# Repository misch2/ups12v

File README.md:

# Goal

A hobby project to create simple 12 V UPS to backup my router and mini PC. Both appliances use 12 volts on input. 
This UPS:
 - should be powered by 18650 batteries
 - does not need to run for a long time, 15 minutes is perfectly OK, 30 minutes is luxury
 - should allow some sort of monitoring, ideally with an HomeAssistant integration (for charts etc.)
 - should provide at least this amount of power
   - 1A (for router)
   - or 3A (for mini PC)
 - should run primarily from the main source and switch to the batteries only when the main voltage drops. This is to protect the batteries and charging circuit so that it doesn't need to constantly provide relatively high power for a device.
 - might allow powering off itself on request when running on batteries, to allow mini PC to automatically power on later after a shutdown.

# Features

 - Can be controlled and monitored using HomeAssistant (ESP32C3 chip, ESPHome software)
 - 12 V / 3 A output
 - (optional) SW controllable output poweroff, can be used to power cycle the device attached to UPS
 - (optional) Battery calibration, i.e. one-off measuring of real available battery capacity.
 - (optional) UPS cut off on power loss and low battery, to allow for a full shutdown of both UPS and the attached device.

# Inspiration
* https://www.hackster.io/news/a-diy-mini-ups-for-wi-fi-router-9b8f11540294
* https://digitalab.org/2021/08/router-ups/
* Lithium battery charger module (12W, 3A) with 5V to 12V booster from Aliexpress:
https://vi.aliexpress.com/item/1005005742927465.html?gatewayAdapt=glo2vnm

# Version 1

Deployed to production, used for a backup of my Archer C6 router only. 
But it's mostly a proof of concept, with power limitations and without a proper PCB (components are just wired up together).

Schema: [schema_v1.pdf](hardware/v1/schema.pdf)

Some photos: [photo1](hardware/v1/IMG_20240301_100945.jpg), [photo2](hardware/v1/IMG_20240302_140645.jpg), [photo3](hardware/v1/IMG_20240302_140731.jpg).

"boosterEnable" input is there not to save power but to prevent running the XL6009 booster in an undervoltage condition. This could have been implemented using a voltage comparator (LM311?) + schmitt trigger for hysteresis. I used software solution because tbne undervoltage condition doesn't occur "suddenly" but it's only a startup condition. And using software to control it allows me to use it for powering off the UPS when it runs on battery.

## Development progress

Replaced AMS1117 with a buck converter due to a large voltage difference and therefore large heat dissipation with LDO.

Added XL6009 "EN" pin control (initial pull down + software control from ESP32).

Used Schottky diodes.

Added a diode between battery power line and XL6009 to prevent backpropagation of voltage when XL6009 is powered down.

The limitations were caused by:
 - BMS module for 18650 batteries can handle only 2A (FIXME?) of current. This is not enough for the mini PC.
 - INA219 module can handle only 3.2A of current. Again, this is not enough for the mini PC (especially not for the battery side of the UPS where the max current can easily be larger).
 - The specific XL6009 booster module doesn't have an undervoltage protection and it can produce more than 12 V on it's output when the input voltage is low. This is not good!

Anyway, this works well for the router. It can run for more than 2 hours from batteries because the router consumes only about 3 watts and the output current is therefore mostly below 300 mA. So I might call this a success ✅!

# Version 1.5

I wanted to overcome the limitations of the first version and to make it handle larger current to power the mini PC which might need up to 3 A. This higher current would also require something better than the INA219.

I also added relays to allow the UPS to be powered off completely when running on batteries. This is to allow the mini PC to power on automatically after a power outage. And a 2nd relay allows to power cycle the UPS or to run calibration.

ACS712 sensors paired with an ADS1115 ADC are used for current and voltage monitoring. It can handle up to 20 A. 

A pair of XL74610 ideal diodes is used instead of Schottky diodes in v1, to achieve a lower voltage drop and to allow for higher currents.

TP5100 charger module is used for charging the batteries, combined with BMS for 2S 8.4V/20A.

Alas, while everything looked good on the paper, reality was different ❌. The "better" booster module ([LM2587 version](https://www.laskakit.cz/step-up-boost-menic-lm2587--4-30v-30w/)) advertises up to 5A and 30W, but something might be wrong with it. I'm not able to pull more than 1 A from the UPS, the voltage drastically drops if I try to pull more.

Possible causes (investigating ⌛):
 - Batteries don't provide enough current? Not very probable, I'm using 3000 mAh cells from a reputable manufacturer.
 - BMS module can't handle the current? It should be able to handle 20 A but does it?
 - Booster module can't handle the current? It should be able to handle 5 A but does it?
 - Something else?

An idea: disconnect the LM2587 booster and attach an electronic load to the battery instead of it. Then try to pull whatever it takes to see if the batteries can provide the current. If they can, then the problem is with the booster. If they can't, then the problem is with the batteries or BMS.

Result: ⌛

# FIXME TODO 

Maybe this was a completely bad approach. Sticking to 2x 18650 doesn't make sense if I need to pull 3 A. I should have used 4S 18650 (13.6 V - 16.8 V) and eliminate the boost converter completely. When stepping down to 12 V, the current would be lower and the voltage drop would be lower.
Also no need to stick with 12 V and a boost converter on input.

# Version 2

Using **BQ25798** battery charger IC from Texas Instruments. According to the datasheet it can handle up to 5 A on the output and 3A on the input and has a built-in buck-boost converter usable for either battery charging or for the UPS backup mode. It can also be controlled and monitored extensively using I2C.

Product info: https://www.ti.com/product/BQ25798

Most important features:
* Buck-boost charger for 1-4 cell batteries
* Narrow voltage DC (NVDC) power path
* Backup Mode with Ultra-fast switchover to adjustable voltage
* Flexible autonomous and I2C mode for optimal system performance
* Intelligent current management to prevent source overload when charging batteries
* Integrated 16-bit ADC for voltage, current, and temperature monitoring

It's essentially a battery charger capable of using boost converter to charge the batteries, but it can also detect a drop in input voltage and switch to the backup mode aka battery mode very fast. In the backup mode it works as buck converter and uses the batteries to power the load.

So, theoretically, with this IC I can eliminate all the former external circuitry because BQ25798 will take care of both charging the batteries and providing power to the load. And it has hundreds of I2C registers to set up and monitor the system.

#### Normal mode power path:

#### Backup mode power path:

#### Inductor selection

See page 133 of datasheet:

```
L = 2.2 µH (only two inductor values are available: 2.2 µH and 1 µH)

Isat >= MAX((Iin + Iripple/2), Ichg + Iripple/2)

Iripple_buck = Vsys / Vbus * (Vbus - Vsys) / (Fsw * L)
Iripple_boost = Vbus /Vsys * (Vsys - Vbus) / (Fsw * L)
```

For my purposes (12 V input, 12 V output, 4S Li-Ion battery pack, 3 A power source) the values are:

```
Iin = 3 A (input current)
Vbus = 12 V (input voltage)
Vsys = +16.8 V (battery voltage)

Iripple_buck = 12 V / 16.8 V * (16.8 V - 12 V) / (750 kHz * 2.2 uH) = 3.43 / 1.65 = 2.08 A
Iripple_boost = 16.8 V / 12 V * (12 V - 16.8 V) / (750 kHz * 2.2 uH) = -6.72 / 1.65 = -4.07 A

Isat >= MAX(5.08 A, 7.07 A) = 7.07 A
```

#### PROG resistor selection

See page 25 of datasheet:

2.2 uH inductor requires 750 kHz switching frequency. Therefore the PROG resistor = **27 kOhm** which means:
 - Switching frequency = 750 kHz
 - Cell count: 4
 - ICHG: 1 A
 - VSYSMIN: 12 V
 - VREG: 16.8 V (range 14 V - 18.8 V)

### Principle:

#### Forward (battery charge) mode:

In this mode PMID follows VBUS, i.e. it's not regulated. PMID is also the input to the buck-boost converter. 

#### Battery backup mode:

The FETs between AC1 and VBUS provide reverse blocking (prevents battery voltage from being seen at VBUS). PMID is output of the buck/boost converter.

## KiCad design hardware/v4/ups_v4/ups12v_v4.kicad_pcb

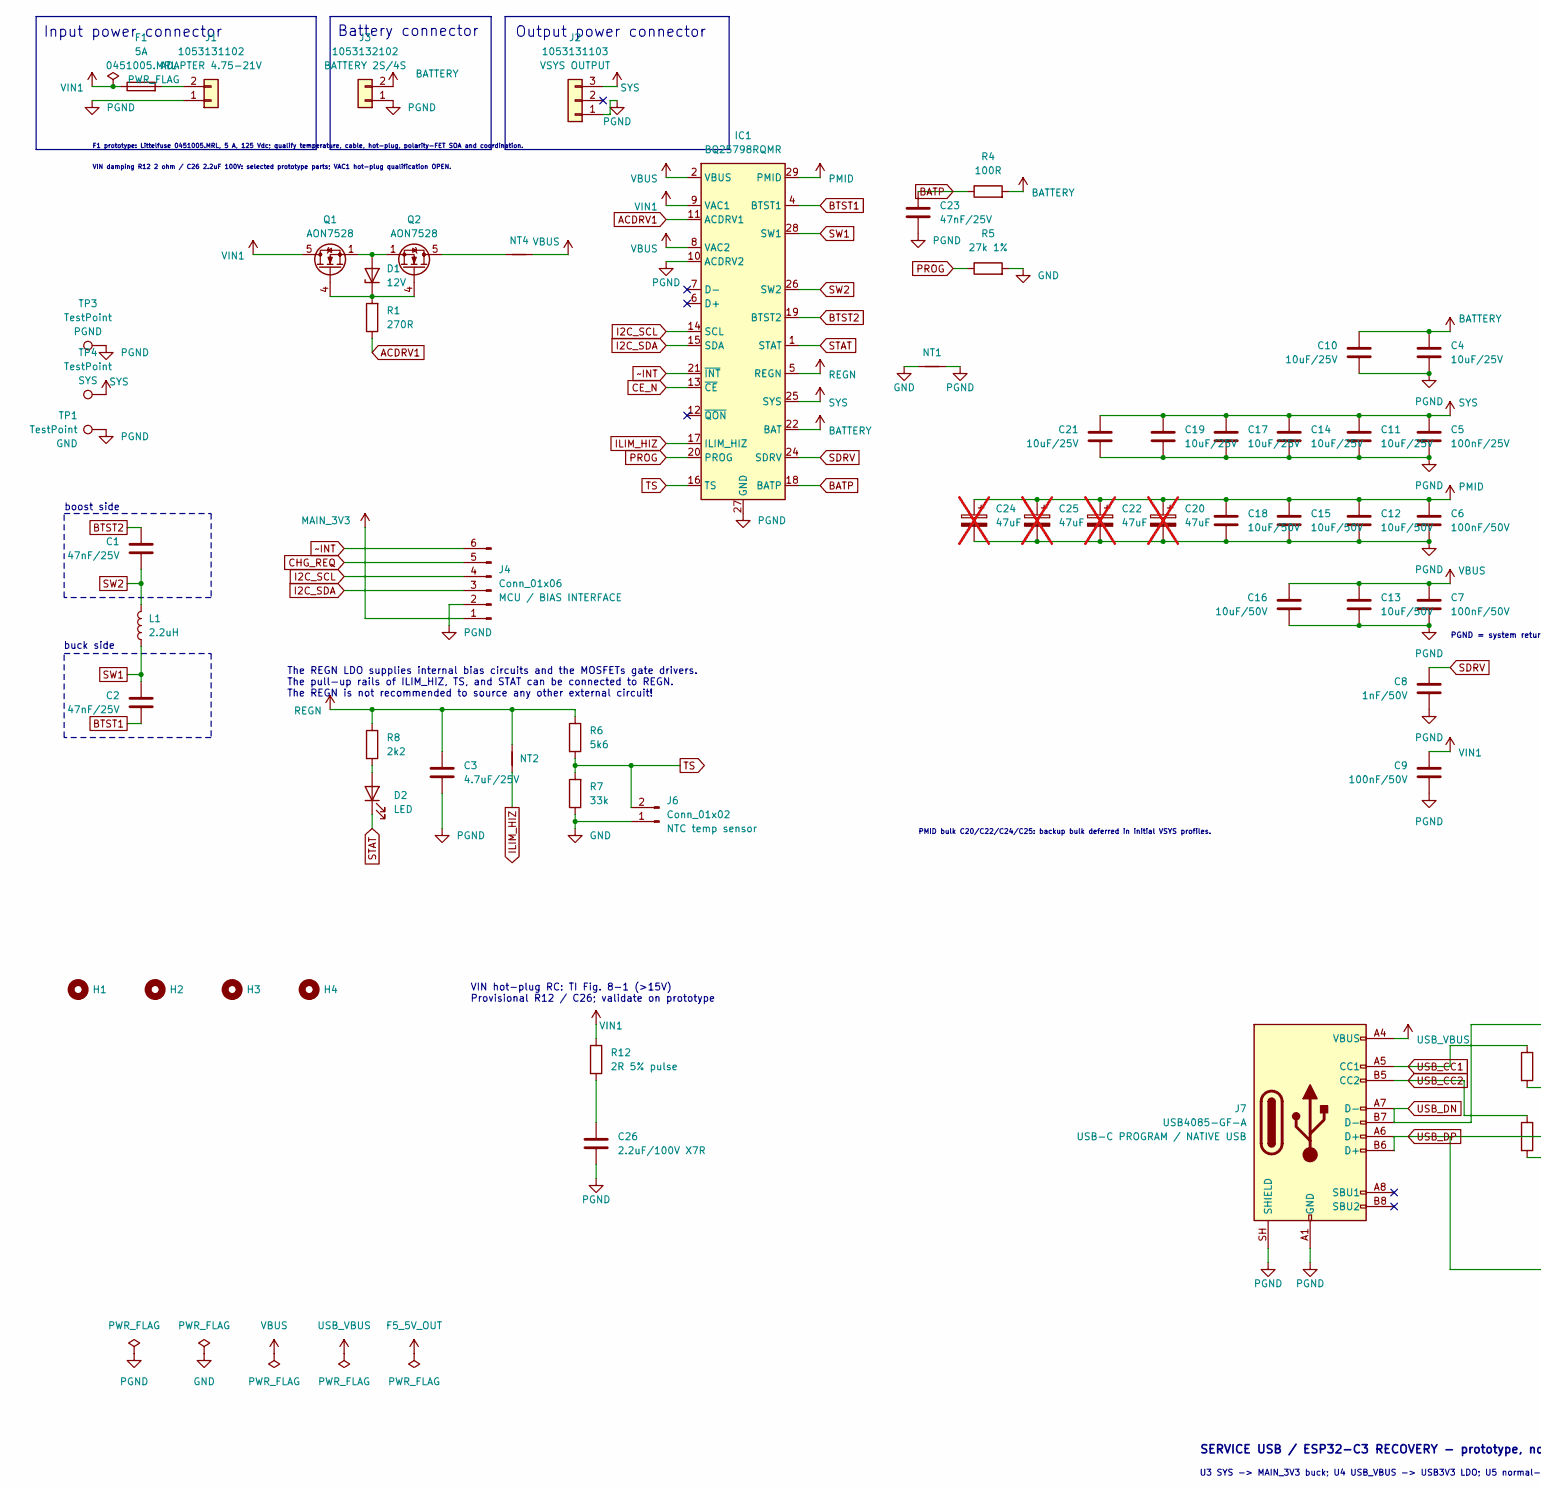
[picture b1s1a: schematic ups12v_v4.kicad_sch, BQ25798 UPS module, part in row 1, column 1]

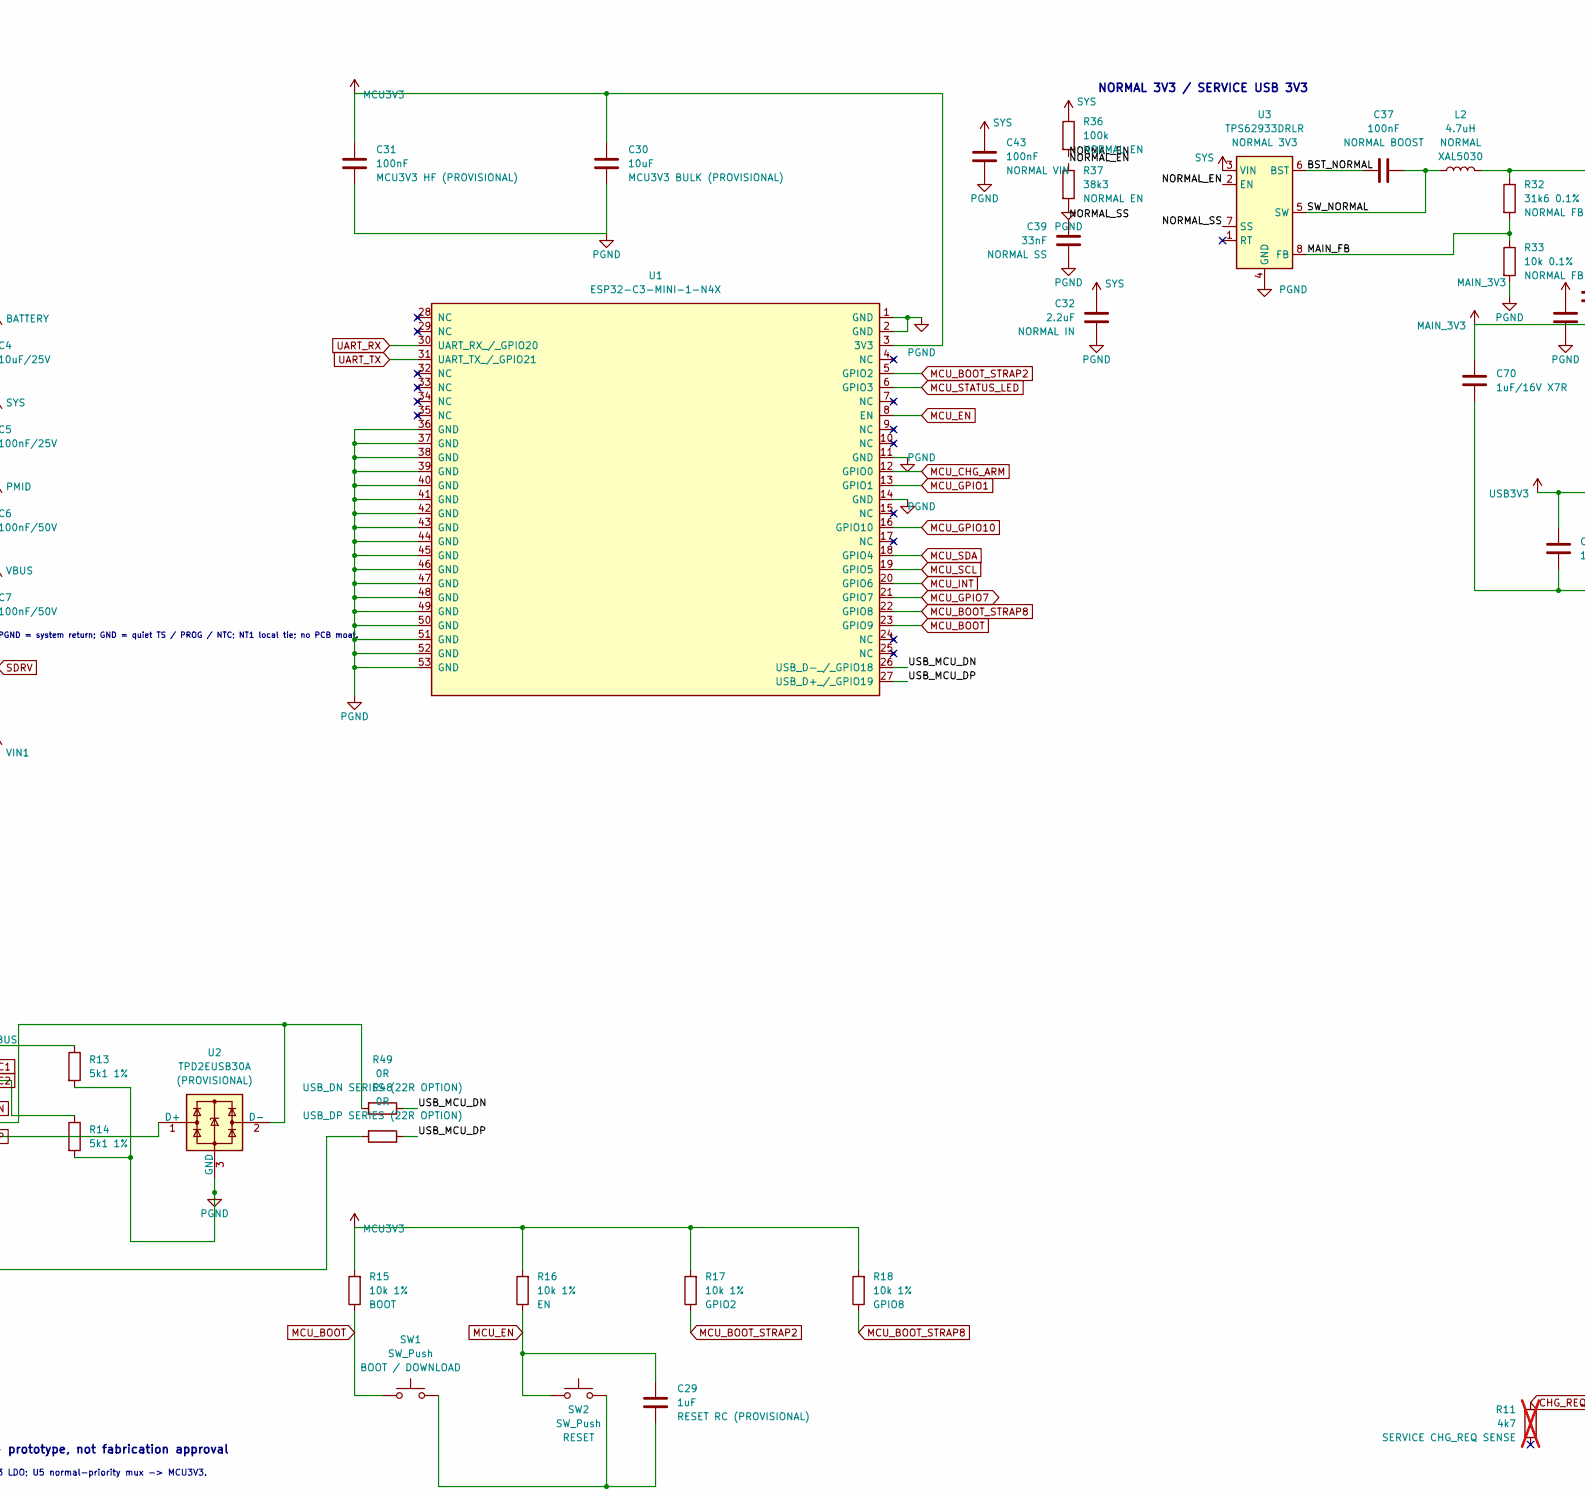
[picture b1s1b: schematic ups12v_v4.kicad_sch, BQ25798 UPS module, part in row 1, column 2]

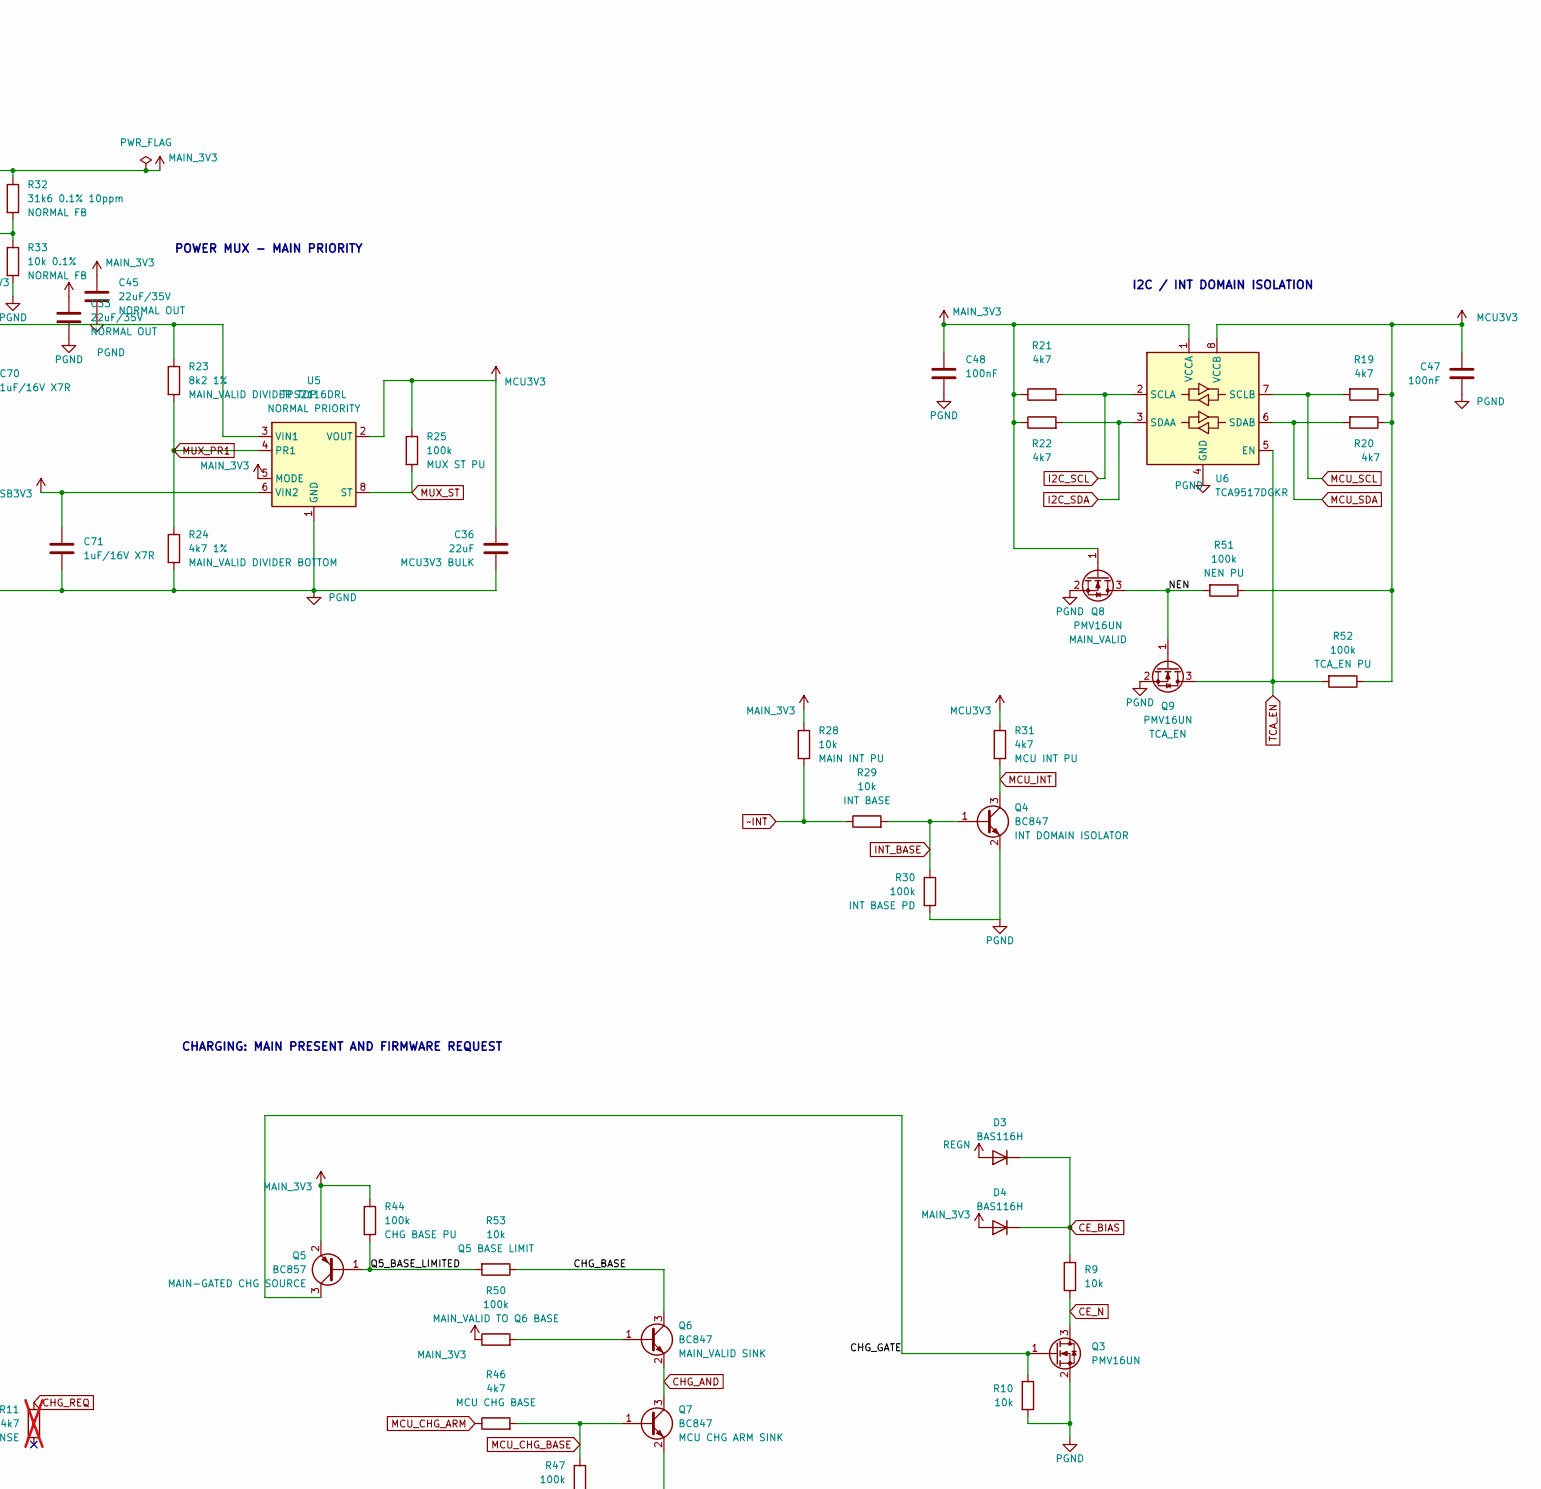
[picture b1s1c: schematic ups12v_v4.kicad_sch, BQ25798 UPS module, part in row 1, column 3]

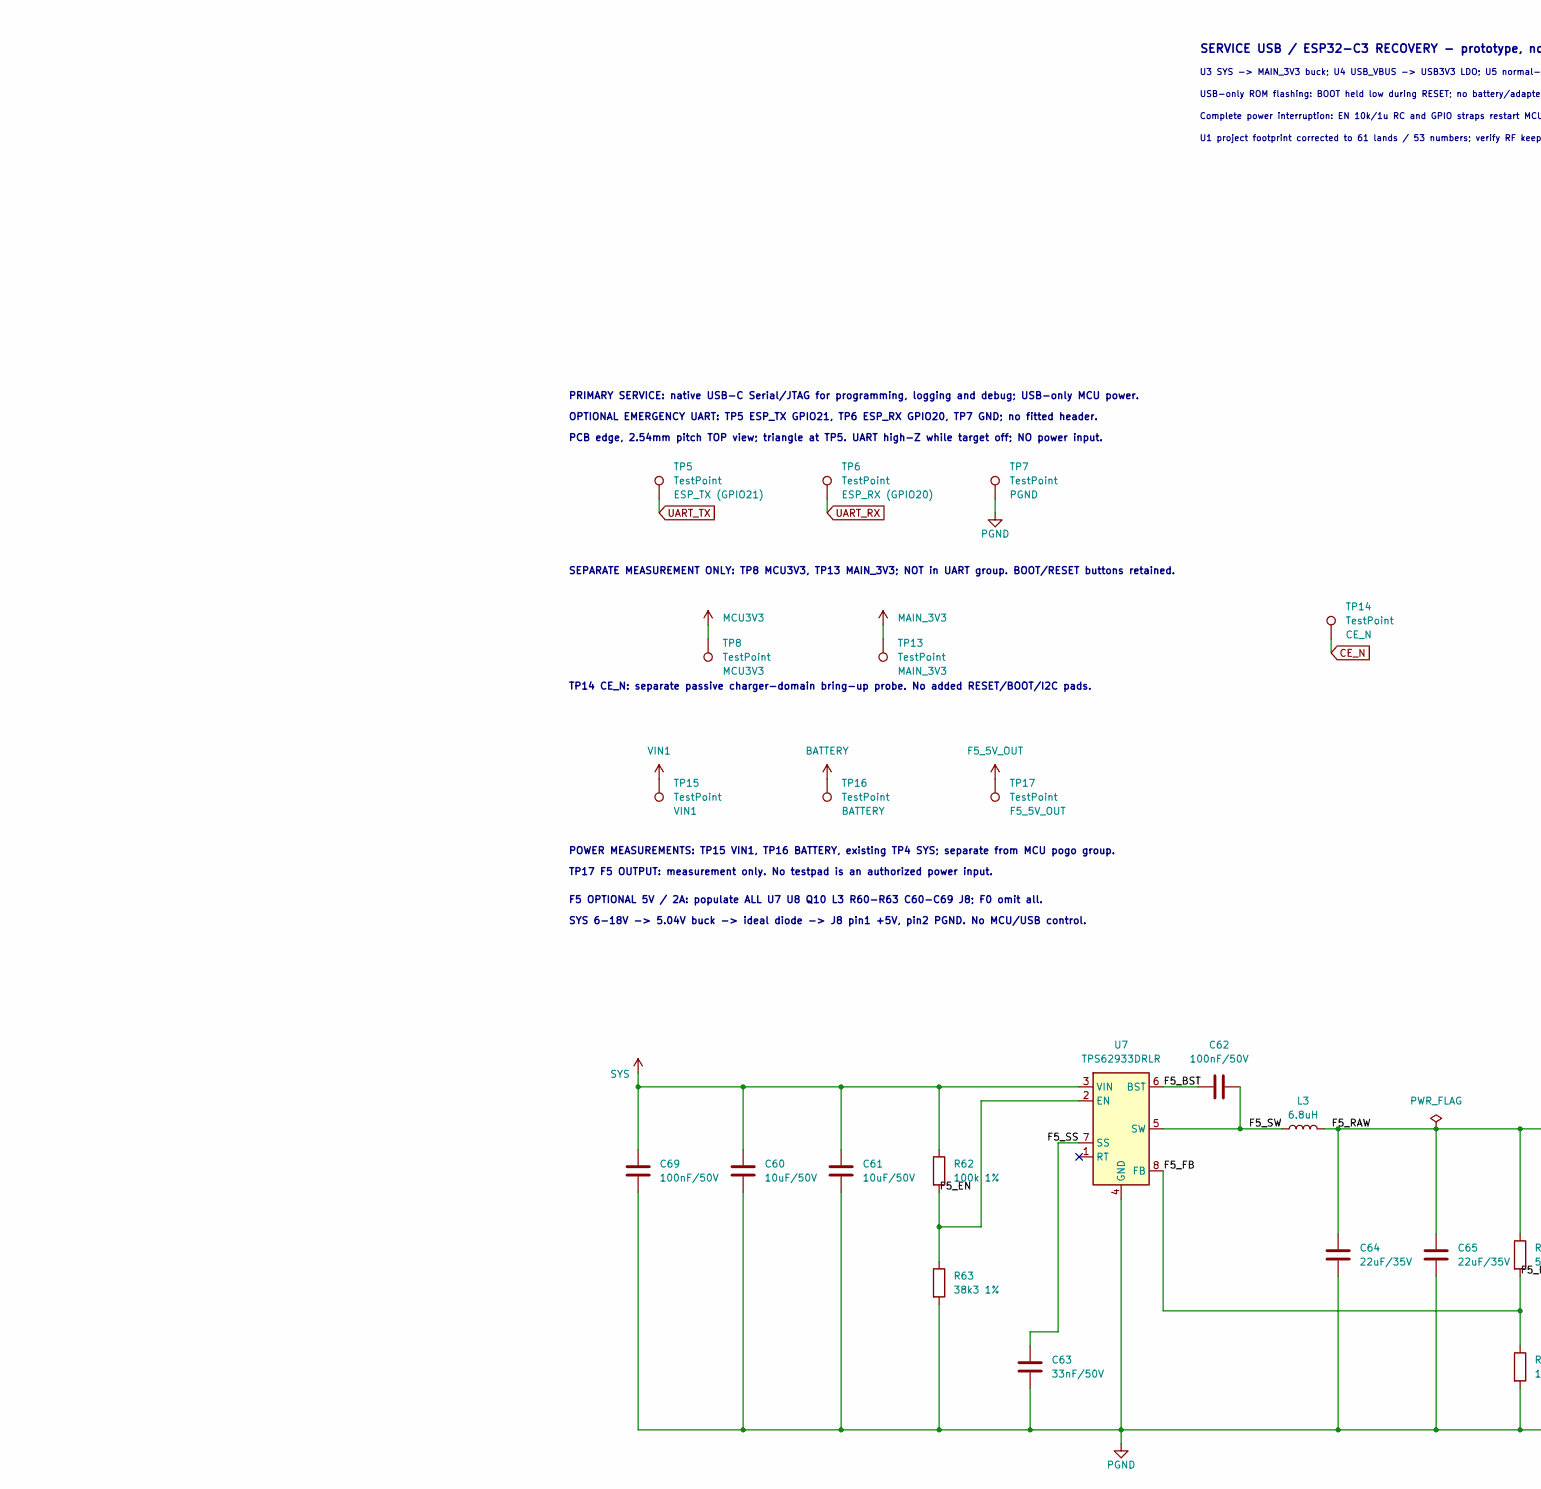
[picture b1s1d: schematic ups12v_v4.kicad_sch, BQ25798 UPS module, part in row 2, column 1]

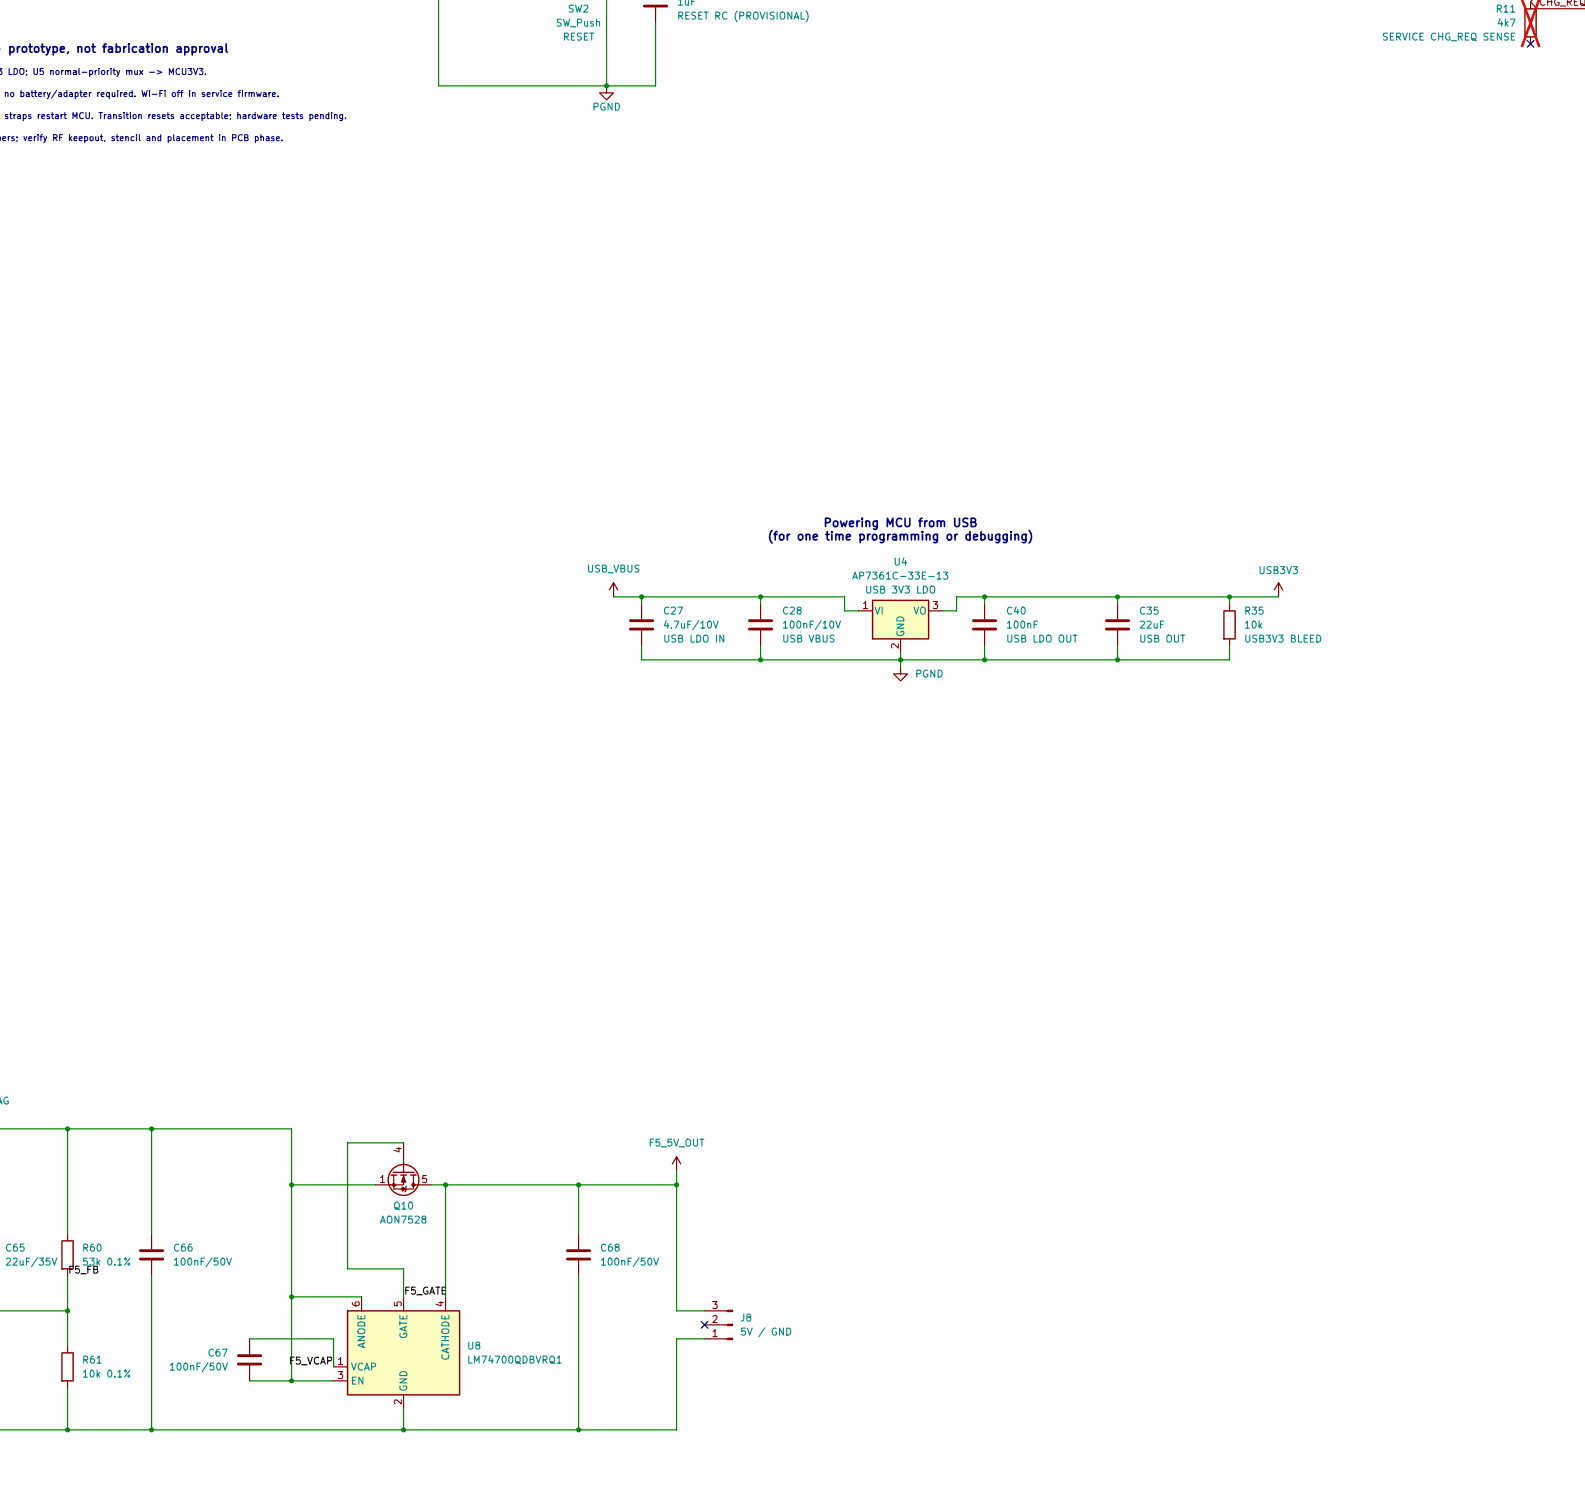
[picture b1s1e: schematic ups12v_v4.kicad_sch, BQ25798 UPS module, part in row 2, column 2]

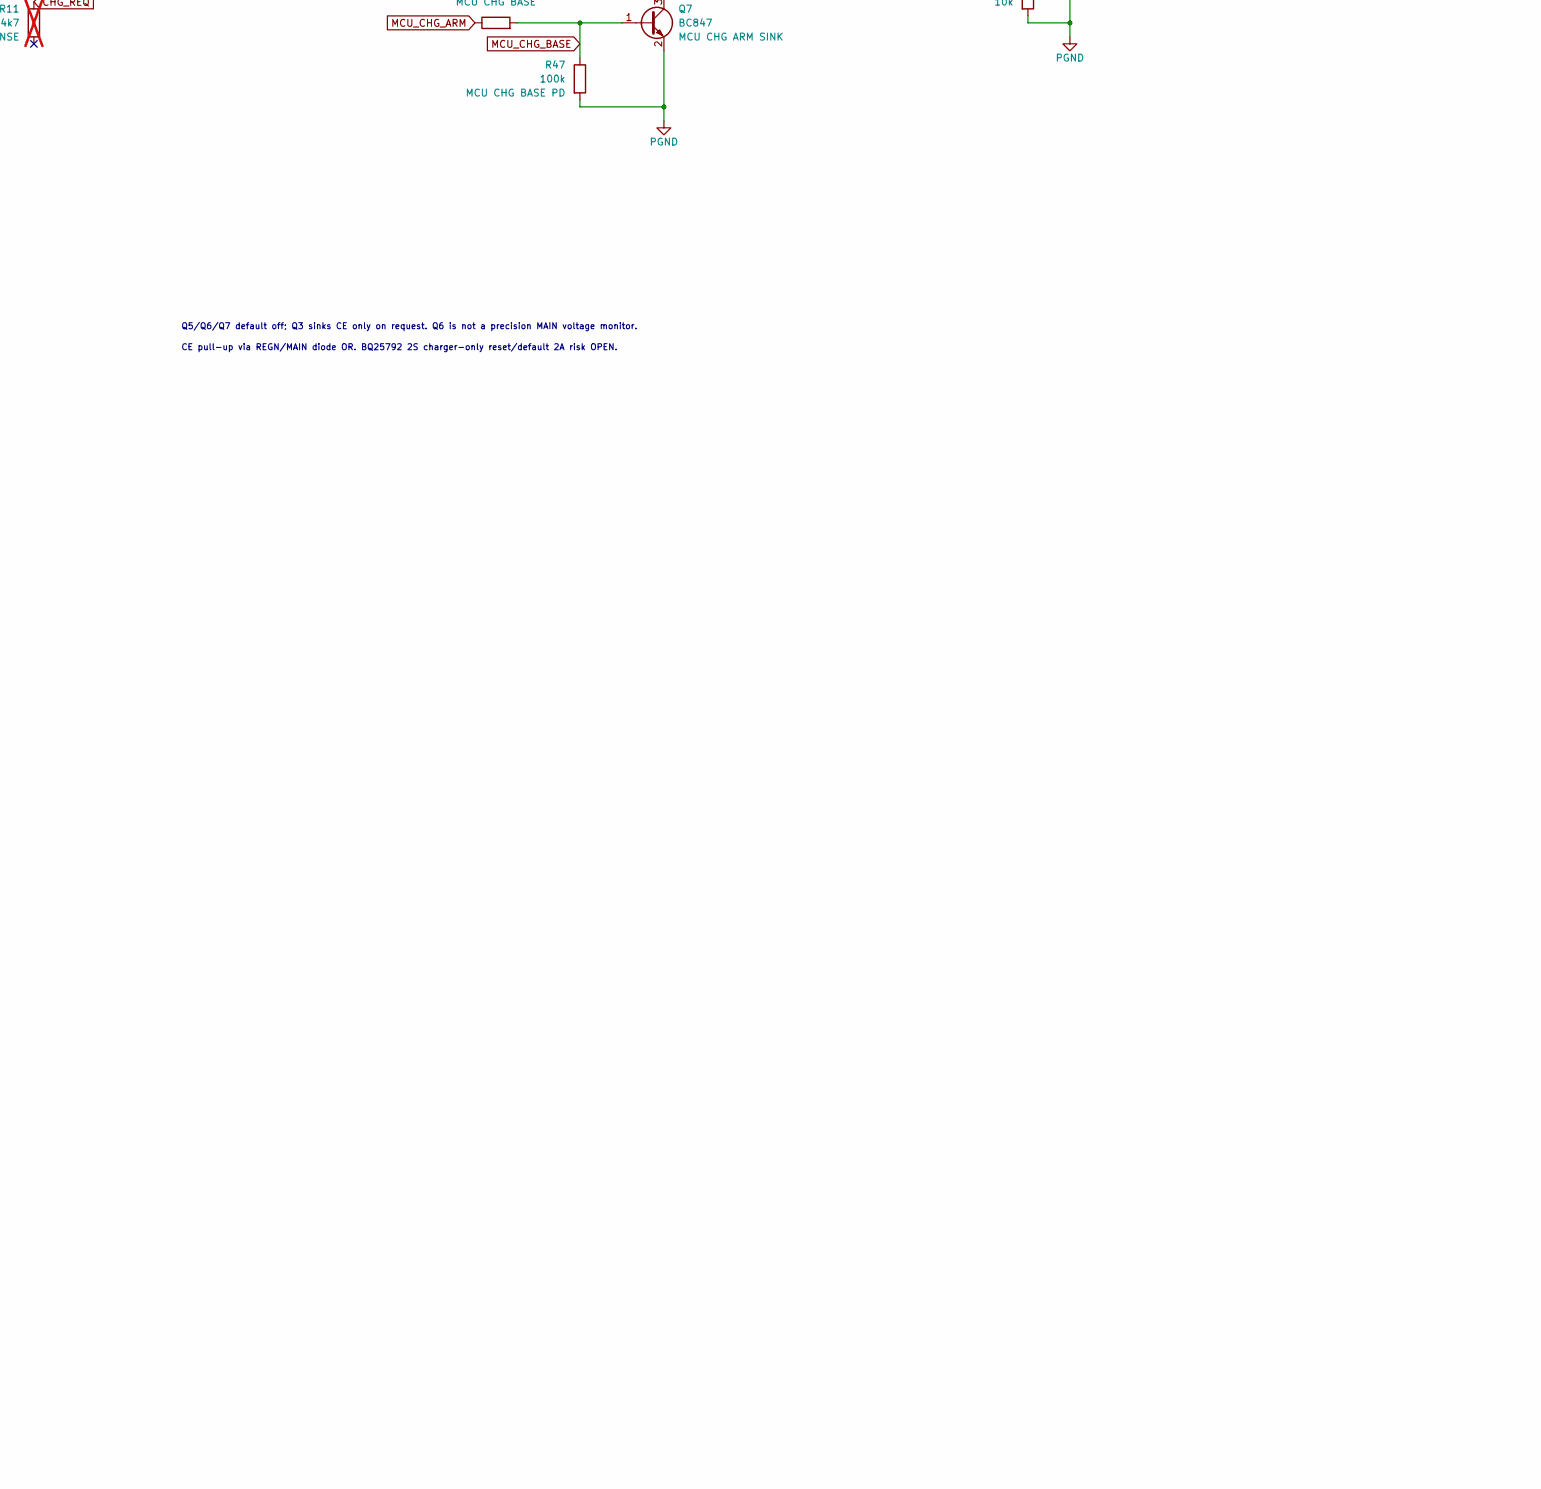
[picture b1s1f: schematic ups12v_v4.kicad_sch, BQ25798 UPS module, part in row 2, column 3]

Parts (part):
C1, C2, C23: 47nF/25V; C_0402_1005Metric
C3: 4.7uF/25V; C_0805_2012Metric; VoltageRating 25V; MPN GRM21BR71E475KA73L
C4, C10, C11, C14, C17, C19, C21: 10uF/25V; C_0805_2012Metric; VoltageRating 25V; MPN GRJ21BR61E106KE01K
C5: 100nF/25V; C_0402_1005Metric
C6, C7, C9: 100nF/50V; C_0402_1005Metric; VoltageRating 50V; MPN GRM155R71H104KE14D
C8: 1nF/50V; C_0402_1005Metric; VoltageRating 50V; MPN GCM1555C1H102JA16D
C12, C13, C15, C16, C18: 10uF/50V; C_1210_3225Metric; VoltageRating 50V; MPN GRM32ER71H106KA12L
C20, C22: 47uF; CASE-D_7343; VoltageRating 20V; MPN 20TQC47MYF; not fitted
C24, C25: 47uF; C_Elec_6.3x5.8; VoltageRating 25V; MPN EEEFK1E470P; not fitted
C26: 2.2uF/100V X7R; C_1210_3225Metric; MPN C1210C225K1RACTU; LCSC Part C2168116
C27: 4.7uF/10V; C_0805_2012Metric; MPN OPEN
C28: 100nF/10V; C_0402_1005Metric; MPN OPEN
C29: 1uF; C_0402_1005Metric; MPN OPEN
C30: 10uF; C_0805_2012Metric; MPN OPEN
C31: 100nF; C_0402_1005Metric; MPN OPEN
C32: 2.2uF; C_0805_2012Metric; MPN OPEN
C33, C45, C64, C65: 22uF/35V; C_1206_3216Metric; MPN C3216X5R1V226M160AC; LCSC Part C69612
C35, C36: 22uF; C_0805_2012Metric; MPN OPEN
C37, C40, C43, C47, C48: 100nF; C_0402_1005Metric
C39: 33nF; C_0402_1005Metric
C60, C61: 10uF/50V; C_1210_3225Metric; MPN GRM32ER71H106KA12L; LCSC Part C77102
C62, C66, C67, C68, C69: 100nF/50V; C_0603_1608Metric; MPN GRM188R71H104KA93D
C63: 33nF/50V; C_0603_1608Metric; MPN GRM188R71H333KA61D
C70, C71: 1uF/16V X7R; C_0603_1608Metric; MPN GRM188R71C105KA12D; LCSC C97890
D1: 12V; D_SOD-123
D2: LED; LED_0805_2012Metric
D3, D4: BAS116H; D_SOD-123F; MPN BAS116H,115
F1: 5A; Littelfuse_451_2410; VoltageRating 125Vdc; 300A interrupt at 32Vdc (2-5A r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; MPN 0451005.MRL
H1, H2, H3, H4: MountingHole; MountingHole_3.2mm_M3_Silk_Keepout
IC1: BQ25798RQMR; Texas_RQM0029A_VQFN-29_4x4mm_P0.4mm; Manufacturer_Part_Number BQ25798RQMR; Mouser Part Number 595-BQ25798RQMR
J1: 1053131102; Molex_Nano-Fit_105313-xx02_1x02_P2.50mm_Horizontal_RevJ1; VoltageRange 4.75-21V at connector; MPN 1053131102
J2: 1053131103; Molex_Nano-Fit_105313-xx03_1x03_P2.50mm_Horizontal_RevJ1; MPN 1053131103; LCSC Part C561764
J3: 1053132102; Molex_Nano-Fit_105313-xx02_1x02_P2.50mm_Horizontal_RevJ1; MPN 1053132102; LCSC Part C17189968
J4: Conn_01x06; JST_XH_S6B-XH-A_1x06_P2.50mm_Horizontal
J6: Conn_01x02; JST_XH_S2B-XH-A-1_1x02_P2.50mm_Horizontal
J7: USB4085-GF-A; USB_C_Receptacle_GCT_USB4085; MPN USB4085-GF-A; LCSC C7095263
J8: 1053132103; Molex_Nano-Fit_105313-xx03_1x03_P2.50mm_Horizontal_RevJ1; MPN 1053132103
L1: 2.2uH; L_12x12mm_H6mm
L2: 4.7uH; L_Coilcraft_XAL5030-XXX; MPN XAL5030-472MEC
L3: 6.8uH; L_Coilcraft_XAL5050-XXX; MPN XAL5050-682MEC
NT1, NT2, NT4: NetTie-2_SMD_Pad0.5mm
Q1, Q2: AON7528; DFN-8_L3.3-W3.3-P0.65-BL-3
Q3, Q8, Q9: PMV16UN; SOT-23; MPN PMV16UN
Q4: BC847; SOT-23; MPN OPEN
Q5: BC857; SOT-23
Q6, Q7: BC847; SOT-23
Q10: AON7528; DFN-8_L3.3-W3.3-P0.65-BL-3; MPN AON7528
R1: 270R; R_0805_2012Metric
R4: 100R; R_0805_2012Metric
R5: 27k 1%; R_0805_2012Metric
R6: 5k6; R_0805_2012Metric
R7: 33k; R_0805_2012Metric
R8: 2k2; R_0805_2012Metric
R9, R10: 10k; R_0805_2012Metric
R11: 4k7; R_0805_2012Metric; not fitted
R12: 2R 5% pulse; R_1206_3216Metric; MPN CRCW12062R00JNEAHP
R13, R14: 5k1 1%; R_0402_1005Metric; MPN OPEN
R15, R16, R17, R18: 10k 1%; R_0402_1005Metric; MPN OPEN
R19, R20, R21, R22, R31: 4k7; R_0402_1005Metric; MPN OPEN
R23: 8k2 1%; R_0402_1005Metric; MPN OPEN
R24: 4k7 1%; R_0402_1005Metric
R25, R30, R50, R51, R52: 100k; R_0402_1005Metric; MPN OPEN
R28, R29, R53: 10k; R_0402_1005Metric; MPN OPEN
R32: 31k6 0.1% 10ppm; R_0402_1005Metric; MPN RN73C1E31K6BTD
R33: 10k 0.1%; R_0402_1005Metric; MPN RN73C1E10KBTD
R35: 10k; R_0402_1005Metric
R36, R44, R47: 100k; R_0402_1005Metric
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
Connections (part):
/BST_NORMAL: C37.1, U3.6 (BST)
/CHG_BASE: Q6.3 (C), R53.1
/CHG_GATE: Q3.1 (G), Q5.3 (C), R10.1
/F5_BST: C62.1, U7.6 (BST)
/F5_EN: R62.2, R63.1, U7.2 (EN)
/F5_FB: R60.2, R61.1, U7.8 (FB)
/F5_GATE: Q10.4 (G), U8.5 (GATE)
/F5_RAW: C64.1, C65.1, C66.1, C67.2, L3.2, Q10.1 (S), Q10.2 (S), Q10.3 (S), R60.1, U8.3 (EN), U8.6 (ANODE)
/F5_SS: C63.1, U7.7 (SS)
/F5_SW: C62.2, L3.1, U7.5 (SW)
/F5_VCAP: C67.1, U8.1 (VCAP)
/MAIN_FB: R32.2, R33.1, U3.8 (FB)
/NEN: Q8.3 (D), Q9.1 (G), R51.2
/NORMAL_EN: R36.2, R37.1, U3.2 (EN)
/NORMAL_SS: C39.1, U3.7 (SS)
/Q5_BASE_LIMITED: Q5.1 (B), R44.2, R53.2
/SW_NORMAL: C37.2, L2.1, U3.5 (SW)
/USB_MCU_DN: R49.1, U1.26 (USB_D-_/_GPIO18)
/USB_MCU_DP: R48.1, U1.27 (USB_D+_/_GPIO19)
ACDRV1: IC1.11 (ACDRV1), R1.1
BATP: C23.1, IC1.18 (BATP), R4.1
BATTERY: C4.1, C10.1, IC1.22 (BAT), IC1.23 (BAT), J3.2, R4.2, TP16.1 (1_1)
BTST1: C2.1, IC1.4 (BTST1)
BTST2: C1.2, IC1.19 (BTST2)
CE_BIAS: D3.1 (K), D4.1 (K), R9.2
CE_N: IC1.13 (~CE), Q3.3 (D), R9.1, TP14.1 (1_1)
CHG_AND: Q6.2 (E), Q7.3 (C)
CHG_REQ: J4.5, R11.1
F5_5V_OUT: C68.1, J8.3, Q10.5 (D), Q10.6 (D), Q10.7 (D), Q10.8 (D), Q10.9 (D), TP17.1 (1_1), U8.4 (CATHODE)
GND: J6.1, NT1.1, R5.2, R7.1
I2C_SCL: IC1.14 (SCL), J4.4, R21.2, U6.2 (SCLA)
I2C_SDA: IC1.15 (SDA), J4.3, R22.2, U6.3 (SDAA)
ILIM_HIZ: IC1.17 (ILIM_HIZ), NT2.1
INT_BASE: Q4.1 (B), R29.2, R30.1
MAIN_3V3: C33.1, C45.1, C48.1, C70.1, D4.2 (A), J4.1, L2.2, Q5.2 (E), Q8.1 (G), R21.1, R22.1, R23.1, R28.1, R32.1, R44.1, R50.1, TP13.1 (1_1), U5.3 (VIN1), U5.5 (MODE), U6.1 (VCCA)
MCU3V3: C30.1, C31.1, C36.1, C47.1, R15.2, R16.2, R17.2, R18.2, R19.1, R20.1, R25.1, R31.1, R51.1, R52.1, TP8.1 (1_1), U1.3 (3V3), U5.2 (VOUT), U5.7 (VOUT), U6.8 (VCCB)
MCU_BOOT: R15.1, SW1.1, U1.23 (GPIO9)
MCU_BOOT_STRAP2: R17.1, U1.5 (GPIO2)
MCU_BOOT_STRAP8: R18.1, U1.22 (GPIO8)
MCU_CHG_ARM: R46.1, U1.12 (GPIO0)
MCU_CHG_BASE: Q7.1 (B), R46.2, R47.1
MCU_EN: C29.1, R16.1, SW2.1, U1.8 (EN)
MCU_GPIO1: U1.13 (GPIO1)
MCU_GPIO7: U1.21 (GPIO7)
MCU_GPIO10: U1.16 (GPIO10)
MCU_INT: Q4.3 (C), R31.2, U1.20 (GPIO6)
MCU_SCL: R19.2, U1.19 (GPIO5), U6.7 (SCLB)
MCU_SDA: R20.2, U1.18 (GPIO4), U6.6 (SDAB)
MCU_STATUS_LED: U1.6 (GPIO3)
MUX_PR1: R23.2, R24.1, U5.4 (PR1)
MUX_ST: R25.2, U5.8 (ST)
unnamed: C26.1, R12.2
unnamed: D1.2 (A), Q1.1 (S), Q1.2 (S), Q1.3 (S), Q2.1 (S), Q2.2 (S), Q2.3 (S)
unnamed: D1.1 (K), Q1.4 (G), Q2.4 (G), R1.2
unnamed: D2.2 (A), R8.2
unnamed: F1.2, J1.2
unnamed: NT4.2, Q2.5 (D), Q2.6 (D), Q2.7 (D), Q2.8 (D), Q2.9 (D)
unnamed: Q6.1 (B), R50.2
PGND: C3.2, C4.2, C5.2, C6.2, C7.2, C8.2, C9.2, C10.2, C11.2, C12.2, C13.2, C14.2, C15.2, C16.2, C17.2, C18.2, C19.2, C20.2, C21.2, C22.2, C23.2, C24.2, C25.2, C26.2, C27.2, C28.2, C29.2, C30.2, C31.2, C32.2, C33.2, C35.2, C36.2, C39.2, C40.2, C43.2, C45.2, C47.2, C48.2, C60.2, C61.2, C63.2, C64.2, C65.2, C66.2, C68.2, C69.2, C70.2, C71.2, IC1.10 (ACDRV2), IC1.27 (GND), J1.1, J2.1, J3.1, J4.2, J7.A1 (GND), J7.A12 (GND), J7.B1 (GND), J7.B12 (GND), J7.SH (SHIELD), J8.1, NT1.2, Q3.2 (S), Q4.2 (E), Q7.2 (E), Q8.2 (S), Q9.2 (S), R10.2, R13.2, R14.2, R24.2, R30.2, R33.2, R35.2, R37.2, R47.2, R61.2, R63.2, SW1.2, SW2.2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
PMID: C6.1, C12.1, C15.1, C18.1, C20.1, C22.1, C24.1, C25.1, IC1.29 (PMID)
PROG: IC1.20 (PROG), R5.1
REGN: C3.1, D3.2 (A), IC1.5 (REGN), NT2.2, R6.1, R8.1
SDRV: C8.1, IC1.24 (SDRV)
STAT: D2.1 (K), IC1.1 (STAT)
SW1: C2.2, IC1.28 (SW1), L1.2
SW2: C1.1, IC1.26 (SW2), L1.1
SYS: C5.1, C11.1, C14.1, C17.1, C19.1, C21.1, C32.1, C43.1, C60.1, C61.1, C69.1, IC1.25 (SYS), J2.3, R36.1, R62.1, TP4.1 (1_1), U3.3 (VIN), U7.3 (VIN)
TCA_EN: Q9.3 (D), R52.2, U6.5 (EN)
TS: IC1.16 (TS), J6.2, R6.2, R7.2
UART_RX: TP6.1 (1_1), U1.30 (UART_RX_/_GPIO20)
UART_TX: TP5.1 (1_1), U1.31 (UART_TX_/_GPIO21)
USB3V3: C35.1, C40.1, C71.1, R35.1, U4.3 (VO), U5.6 (VIN2)
USB_CC1: J7.A5 (CC1), R13.1
USB_CC2: J7.B5 (CC2), R14.1
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
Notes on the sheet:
USB-only ROM flashing: BOOT held low during RESET; no battery/adapter required. Wi-Fi off in service firmware.
Powering MCU from USB (for one time programming or debugging)
Complete power interruption: EN 10k/1u RC and GPIO straps restart MCU. Transition resets acceptable; hardware tests pending.
U3 SYS -> MAIN_3V3 buck; U4 USB_VBUS -> USB3V3 LDO; U5 normal-priority mux -> MCU3V3.
Output power connector
POWER MUX - MAIN PRIORITY
NORMAL 3V3 / SERVICE USB 3V3
Battery connector
VIN damping R12 2 ohm / C26 2.2uF 100V: selected prototype parts; VAC1 hot-plug qualification OPEN.
boost side
TP17 F5 OUTPUT: measurement only. No testpad is an authorized power input.
I2C / INT DOMAIN ISOLATION
POWER MEASUREMENTS: TP15 VIN1, TP16 BATTERY, existing TP4 SYS; separate from MCU pogo group.
Input power connector
Q5/Q6/Q7 default off; Q3 sinks CE only on request. Q6 is not a precision MAIN voltage monitor.
SYS 6-18V -> 5.04V buck -> ideal diode -> J8 pin1 +5V, pin2 PGND. No MCU/USB control.
SEPARATE MEASUREMENT ONLY: TP8 MCU3V3, TP13 MAIN_3V3; NOT in UART group. BOOT/RESET buttons retained.
VIN hot-plug RC: TI Fig. 8-1 (>15V) Provisional R12 / C26; validate on prototype
OPTIONAL EMERGENCY UART: TP5 ESP_TX GPIO21, TP6 ESP_RX GPIO20, TP7 GND; no fitted header.
U1 project footprint corrected to 61 lands / 53 numbers; verify RF keepout, stencil and placement in PCB phase.
PMID bulk C20/C22/C24/C25: backup bulk deferred in initial VSYS profiles.
F1 prototype: Littelfuse 0451005.MRL, 5 A, 125 Vdc; qualify temperature, cable, hot-plug, polarity-FET SOA and coordination.
TP14 CE_N: separate passive charger-domain bring-up probe. No added RESET/BOOT/I2C pads.
PRIMARY SERVICE: native USB-C Serial/JTAG for programming, logging and debug; USB-only MCU power.
CHARGING: MAIN PRESENT AND FIRMWARE REQUEST
buck side
PGND = system return; GND = quiet TS / PROG / NTC; NT1 local tie; no PCB moat.
F5 OPTIONAL 5V / 2A: populate ALL U7 U8 Q10 L3 R60-R63 C60-C69 J8; F0 omit all.
SERVICE USB / ESP32-C3 RECOVERY - prototype, not fabrication approval
The REGN LDO supplies internal bias circuits and the MOSFETs gate drivers. The pull-up rails of ILIM_HIZ, TS, and STAT can be connected to REGN. The REGN is not recommended to source any other external circuit!
CE pull-up via REGN/MAIN diode OR. BQ25792 2S charger-only reset/default 2A risk OPEN.
PCB edge, 2.54mm pitch TOP view; triangle at TP5. UART high-Z while target off; NO power input.

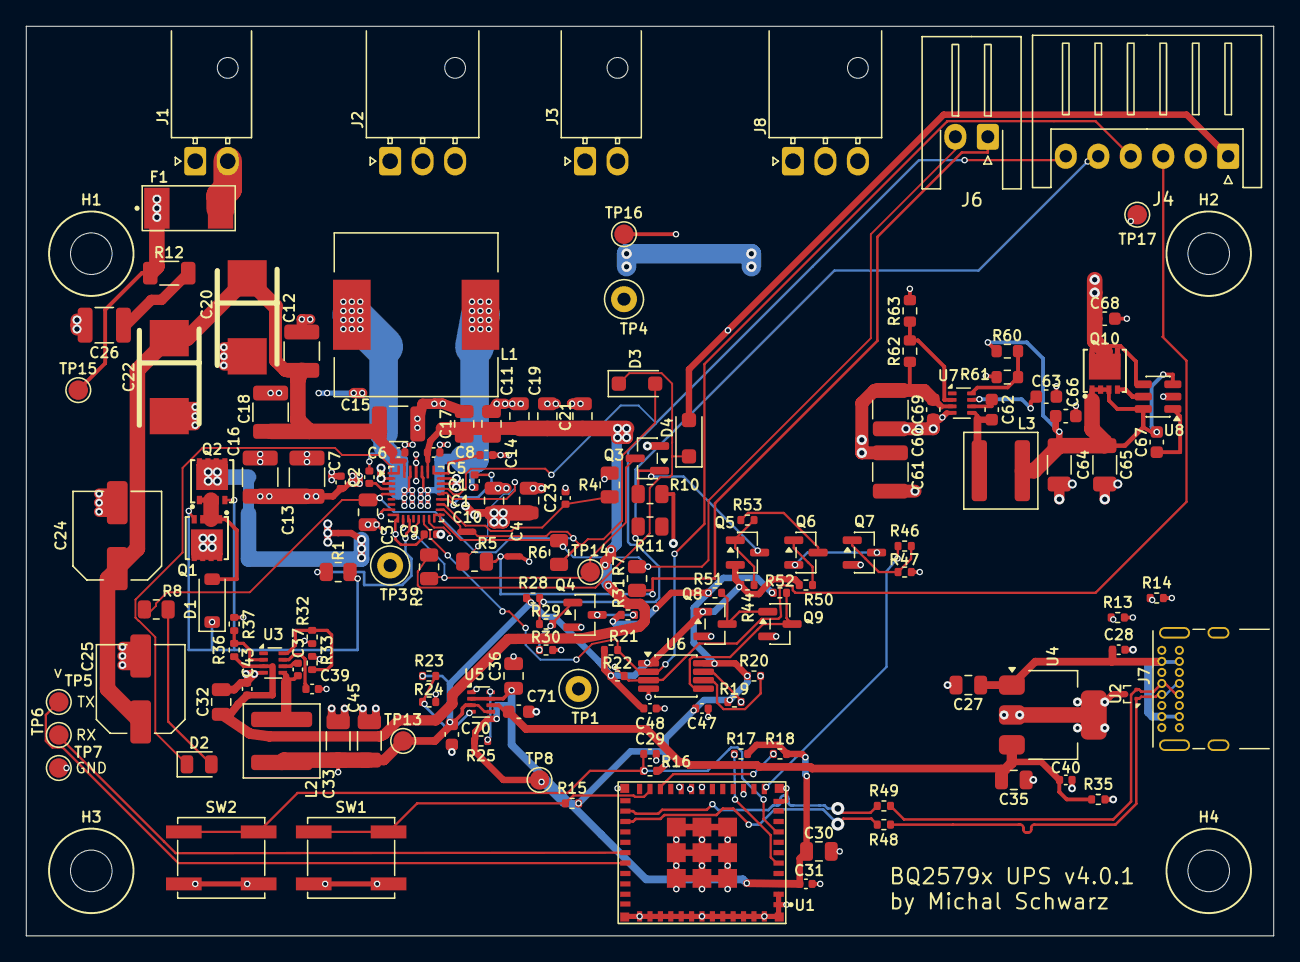
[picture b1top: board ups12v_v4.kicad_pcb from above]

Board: 4 copper layers, 96.0 x 70.0 mm, 154 parts (0 on the bottom side), 76 nets.
